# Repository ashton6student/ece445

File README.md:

# VR Gloves Project

Note: each subfolder has its own `README.md` file that forms the ECE 445 notebook, in addition to this top-level file.

## Overview

The VR Gloves project aims to create a pair of wearable hand-tracking gloves for VR applications, compatible with popular VR systems like Meta Quest 2. The gloves utilize perpendicular Hall effect sensors and magnets for finger flex tracking, a servo-based haptic feedback system, and BLE communication to interact with Unity applications.

## Inspirations

This project is inspired by LucidGloves, an open-source VR glove. This project specifically attempts to take the good things from V3 and the good things from V5 to make our own unique solution. Specifically, it uses the badge reel idea from V3 and the hall-effect magnet solution from the V5 and combines them together.

## Problem Statement

Modern VR devices often rely on handheld controllers that do not fully immerse the user in the virtual environment. While some high-end solutions like the Valve Index offer partial finger tracking, most affordable options still use conventional button-based input. The goal of this project is to develop a more immersive and affordable solution using DIY components.

## Key Features

- **Wireless Communication:** Uses BLE to transmit hand data to Unity applications.
- **Finger Tracking:** Perpendicular Hall effect sensors measure finger curl using magnetic field angle changes.
- **Haptic Feedback:** Servo motors lock the badge reels, restricting finger movement to provide haptic feedback.
- **Integrated VR Interaction:** Uses Unity's XR Interaction Toolkit to allow for these gloves to be developed in a VR scene and can be deployed to a VR headset.

## System Design

The VR gloves consist of five main subsystems:

### 1. Power Subsystem

- Uses a 7.4V Li-ion battery stepped down to 5V and 3.3V using LDO regulators.
- Provides stable power for ESP32-S3, hall effect sensors, and servo motors.

### 2. Sensor Subsystem

- Perpendicular Hall effect sensors paired with magnets on each finger track the degree of bend.
- Quest Controller used for hand positioning.
- Haptic feedback provided by servos locking badge reels.

### 3. MCU Subsystem

- Uses ESP32-S3 for data acquisition, BLE communication, and haptic control.
- Converts raw sensor data into a usable format in Unity.
- Transmits data via BLE to Unity with low latency (<20ms).

### 4. Controller Subsystem

- Features a thumb joystick and push buttons mounted on the index finger.
- Allows for conventional VR controller actions.
- Data is transmitted to Unity using the BLE protocol.

### 5. Software Subsystem

- Integrates with Unity using the XR Interaction Toolkit for virtual scene deployment.
- Virtual scene containing objects with colliders to test interaction.
- BLE data mapped to virtual hand movements and actions.
- Collision detection triggers haptic feedback via BLE.

## Code Structure

```
project_root/
├── Unity Files/       # Unity project and scenes
├── PCB Files/         # PCB schematics and board files
├── Arduino Files/     # Arduino sketches for glove firmware
├── 3D Files/          # 3D models and assets for Unity
├── Bluetooth Files/   # BLE communication scripts and libraries
├── myenv/             # Virtual environment for Python utilities
└── README.md          # Project documentation
```

### Arduino Files and Bluetooth Files

- Contains Arduino sketches for ESP32 to handle BLE communication and haptic control.
- Implements data acquisition from Hall effects and joystick inputs.
- Supports BLE wireless communication for real-time data transfer.

### Unity Files

- Unity scripts for receiving BLE data and controlling virtual hands.
- Includes a test scene for verifying glove performance.

### 3D Files

- 3D files for the glove parts.

### PCB Files

- KiCAD files for the PCBs in our project.

## Installation

1. Flash the ESP32 with the provided firmware in the `firmware/glove_controller/` directory.
2. Run the BLE Python bridge script located in `Bluetooth Files/`. You may need com2com software to simulate serial ports. Be sure to activate the Python virtual environment in `myenv/` and install required packages.
3. Open the Unity project from the `Unity Files/` folder.
4. Run the scene to test the glove inputs.

## Usage

- Wear the gloves and ensure they are powered on.
- Start the Unity scene and observe hand movement tracking.
- Test grabbing and manipulating virtual objects to validate haptic feedback.

## Future Improvements

- Enhanced haptic feedback.
- Integration with more VR platforms like SteamVR.
- Improved latency optimization in BLE communication.

## Authors

- Ashton Billings
- Hamza Lutfi
- Aditya Nebhrajani

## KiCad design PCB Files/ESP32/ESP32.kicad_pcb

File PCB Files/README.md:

# PCB Project Overview

This repository contains the design files for two PCBs: **ESP32** and **Hall-Effect Sensor**. Both projects were designed using KiCad and include schematic files, PCB layouts, backups, and Gerber files for manufacturing.

## Project Structure

The repository is structured as follows:

```
PCB Files/
├── ESP32/
│   ├── ESP32.kicad_pcb           # PCB layout file
│   ├── ESP32.kicad_sch           # Schematic file
│   ├── ESP32.kicad_pro           # KiCad project file
│   ├── gerbers/                  # Gerber files for PCB manufacturing
│   └── backups/                  # Backup versions of the project
├── hall-effect/
│   ├── hall-effect.kicad_pcb     # PCB layout file
│   ├── hall-effect.kicad_sch     # Schematic file
│   ├── hall-effect.kicad_pro     # KiCad project file
│   ├── gerbers/                  # Gerber files for PCB manufacturing
│   └── backups/                  # Backup versions of the project
└── __MACOSX/                     # System-generated files (can be ignored)
```

## ESP32 Project

The ESP32 PCB project is designed around the ESP32 microcontroller, featuring:

- BLE and Wi-Fi connectivity
- GPIO headers for peripherals
- Power management circuits

### Gerber Files

The Gerber files located in `ESP32/gerbers/` include:

- Copper layers (F_Cu, B_Cu)
- Silkscreen layers (F_Silkscreen, B_Silkscreen)
- Solder mask layers (F_Mask, B_Mask)
- Paste layers (F_Paste, B_Paste)
- Edge cuts for board outline
- Drill files (PTH, NPTH)

## Hall-Effect Project

This project is based on a Hall-effect sensor module, designed for magnetic field detection.

- Uses a Hall-effect sensor IC
- Signal conditioning circuitry
- Gerber Files

Similar structure to the ESP32 project with copper, silkscreen, mask, paste, edge cuts, and drill files.

## Backups

The `backups/` directories in each project folder contain automated KiCad backups, timestamped for version tracking.

## Usage

Open the project files using KiCad (version 6.x or later). To fabricate the PCBs, use the Gerber files located in the respective `gerbers/` folder.

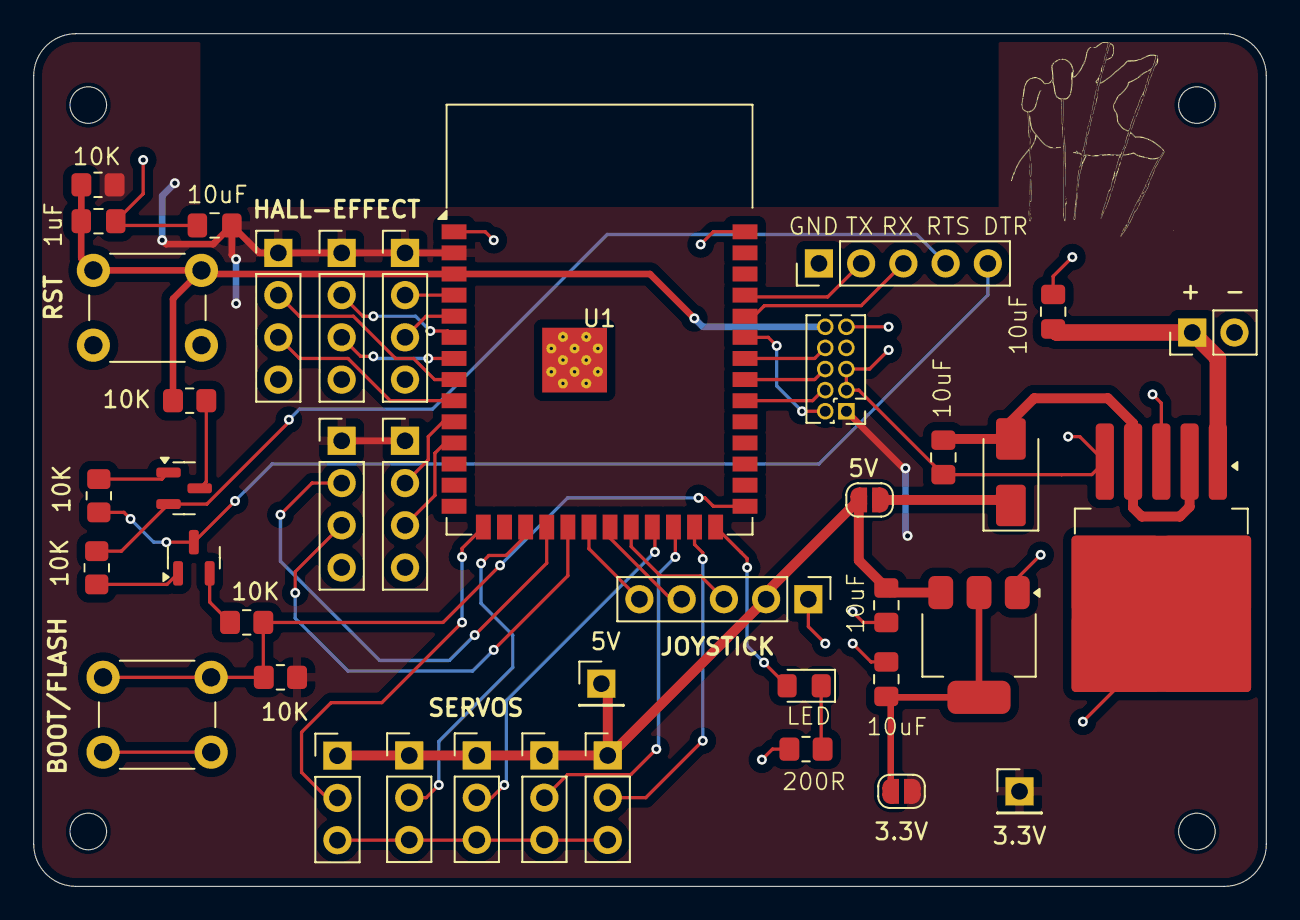
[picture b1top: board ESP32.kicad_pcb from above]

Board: 2 copper layers, 74.1 x 51.3 mm, 44 parts (0 on the bottom side), 41 nets.

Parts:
+: 2S LiPo 7.4V 2000mAh; PinHeader_1x02_P2.54mm_Vertical
C1: 1uF; C_0805_2012Metric_Pad1.18x1.45mm_HandSolder
C2, C3, C5, C6, C7: 10uF; C_0805_2012Metric_Pad1.18x1.45mm_HandSolder
D1: LED; LED_0805_2012Metric_Pad1.15x1.40mm_HandSolder
D2: D_Schottky; D_SMA
H1, H2, H3, H4: MountingHole; MountingHole_2.2mm_M2
J1, J2, J3, J4, J5: Conn_01x03_Pin; PinHeader_1x03_P2.54mm_Vertical
J6, J11: Conn_01x05_Pin; PinHeader_1x05_P2.54mm_Vertical
J7: Conn_ARM_JTAG_SWD_10; PinHeader_2x05_P1.27mm_Vertical
J12, J13, J14, J15, J16: Conn_01x04_Pin; PinHeader_1x04_P2.54mm_Vertical
JP1, JP2: SolderJumper_2_Open; SolderJumper-2_P1.3mm_Open_RoundedPad1.0x1.5mm
Q1, Q2: SS8050; SOT-23
R1, R2, R3, R4, R8, R9: 10k; R_0805_2012Metric_Pad1.20x1.40mm_HandSolder
R5: 200; R_0805_2012Metric_Pad1.20x1.40mm_HandSolder
SW1, SW2: SW_Push; SW_PUSH_6mm
TP1, TP2: TestPoint; PinHeader_1x01_P2.54mm_Vertical
U1: ESP32-S3-WROOM-1
U2: AMS1117-3.3; SOT-223-3_TabPin2
U3: LM2596S-5; TO-263-5_TabPin3

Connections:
+3.3V: C7.2, J7.1 (VTref), J12.1, J13.1, J14.1, J15.1, J16.1, JP2.2 (B), R1.1, R4.2, TP2.1, U1.2 (3V3)
+5V: C3.1, J1.1, J2.1, J3.1, J4.1, J5.1, J11.2, JP1.2 (B), TP1.1, U2.3 (VI)
/0ADC: J13.3, U1.19 (IO11)
/1ADC: J11.5, U1.20 (IO12)
/2ADC: J11.4, U1.21 (IO13)
/3ADC: J11.3, U1.22 (IO14)
/4ADC: J15.2, U1.8 (IO15)
/5ADC: J15.3, U1.9 (IO16)
/6ADC: J16.2, U1.10 (IO17)
/7ADC: J16.3, U1.11 (IO18)
/21: J3.2, U1.23 (IO21)
/45: D1.2 (A), U1.26 (IO45)
/47: J4.2, U1.24 (IO47)
/48: J5.2, U1.25 (IO48)
/ADC2: J1.2, U1.15 (IO3)
/ADC3: J12.2, U1.4 (IO4)
/ADC4: J12.3, U1.5 (IO5)
/ADC5: J14.2, U1.6 (IO6)
/ADC6: J14.3, U1.7 (IO7)
/ADC8: J2.2, U1.17 (IO9)
/ADC9: J13.2, U1.18 (IO10)
/DTR: J6.5, Q2.3 (C), R2.1
/EN: C1.2, J7.10 (~RESET), R1.2, R8.2, SW2.1, U1.3 (EN)
/IO0: R4.1, R9.2, SW1.1, U1.27 (IO0)
/IO39: J7.4 (SWCLK/TCK), U1.32 (IO39)
/IO40: J7.6 (SWO/TDO), U1.33 (IO40)
/IO41: J7.8 (NC/TDI), U1.34 (IO41)
/IO42: J7.2 (SWDIO/TMS), U1.35 (IO42)
/RTS: J6.4, Q1.2 (E), R3.1
/RX: J6.3, U1.36 (RXD0)
/TX: J6.2, U1.37 (TXD0)
GND: +.2 (-), C1.1, C2.2, C3.2, C5.2, C6.2, C7.1, J1.3, J2.3, J3.3, J4.3, J5.3, J6.1, J7.3 (GND), J7.5 (GND), J7.9 (GNDDetect), J11.1, J12.4, J13.4, J14.4, J15.4, J16.4, R5.2, SW1.2, SW2.2, U1.1 (GND), U1.40 (GND), U1.41 (GND), U2.1 (GND), U3.3 (GND), U3.5 (~ON/OFF)
unnamed: +.1 (+), C5.1, U3.1 (VIN)
unnamed: D1.1 (K), R5.1
unnamed: C6.1, D2.2 (A), U3.2 (OUT), U3.4 (FB)
unnamed: D2.1 (K), JP1.1 (A)
unnamed: C2.1, JP2.1 (A), U2.2 (VO)
unnamed: Q1.1 (B), R2.2
unnamed: Q1.3 (C), R8.1
unnamed: Q2.1 (B), R3.2
unnamed: Q2.2 (E), R9.1

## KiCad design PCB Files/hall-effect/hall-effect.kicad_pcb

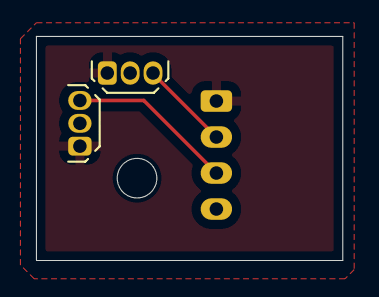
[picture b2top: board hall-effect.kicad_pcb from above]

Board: 2 copper layers, 17.0 x 12.4 mm, 4 parts (1 on the bottom side), 4 nets.

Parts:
H1: MountingHole; MountingHole_2.2mm_M2
J3: Conn_01x04_Socket; JST_PH_S4B-PH-K_1x04_P2.00mm_Horizontal
U1, U2: A1101ELHL; TO-92Flat

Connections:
+3.3V: J3.1, U1.1 (VCC), U2.1 (VCC)
GND: J3.4, U1.2 (VOUT), U2.2 (VOUT)
unnamed: J3.2, U1.3 (GND)
unnamed: J3.3, U2.3 (GND)

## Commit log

2025-03-21 added current work
2025-03-21 fixed a name
2025-03-27 added other arduino files
2025-03-27 fixed arduino file formatting issues for PlatformIO
2025-03-27 Added PlatformIO stuff
2025-03-27 Updated firmware
2025-03-30 Base firmware
2025-03-30 added multi buttons
2025-04-07 updated PCB
2025-04-07 New Hall effect module
2025-04-07 Trace thickness fixed on one of the servos
2025-04-07 Included Gerber files
2025-04-19 Added ino files
2025-04-19 Upped code to 5 floats, included joystick, and added float value override capabilities
2025-04-19 Added print for debugging
2025-04-23 add bluetooth support
2025-04-26 updated code
2025-04-27 updated bridge code
2025-05-03 light change
2025-05-04 Added virtual scene
2025-05-07 add README for bt
2025-05-07 READMEs
2025-05-07 edited READMEs
2025-06-02 stuff
